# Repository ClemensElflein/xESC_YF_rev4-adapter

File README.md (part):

<!-- PROJECT SHIELDS -->
<!--
- Markdown "reference style" links for readability.
- Reference links are enclosed in brackets [ ] instead of parentheses ( ).
  (See the bottom of this document for the declaration of the reference variables)
-->
[![Contributors][contributors-shield]][contributors-url]
[![Forks][forks-shield]][forks-url]
[![Stargazers][stars-shield]][stars-url]
[![Issues][issues-shield]][issues-url]
[![MIT License][license-shield]][license-url]

<!-- PROJECT LOGO -->
<br />
<div align="center">
<h3 align="center">xESC YardForce (Rev4) adapter for <a href="https://github.com/ClemensElflein/OpenMower">OpenMower</a></h3>

  <p align="center">
    Simple xESC adapter for stock Rev4 (built 2017) blade-motor<br>
    (the one with an internal motor controller under its cap)
    <br />
  </p>

  |             v1.x Hardware              |             v2.x Hardware              |
  | :------------------------------------: | :------------------------------------: |
  |  |  |

</div>

<!-- ABOUT THE PROJECT -->
## About The Project

Those who want to use <a href="https://github.com/ClemensElflein/OpenMower">OpenMower</a> with an older YardForce "Rev. 4" (built 2017) model, fail with the stock Blade-Motor as it has an embedded motor-controller under its cap.

It's not very difficult to use this motor:
- Remove stock driver controller
- Wire the coil cables directly
- Add a 5 pin cable to the motor hall sensors
- Connect them to OM's mow-motor-hall-input plug
and use OM's xESC.

But it's somehow "crafted" and you need to be capable to do these things.

As an alternative, this "Adapter" is thought to replace OM's default Mow- xESC.<br>
In addition to this adapter, it's nevertheless **required to exchange two cables of the mow motor cabling**. But this should be also possible for the untalented (see [Requirements](#requirements)).

<p align="right">(<a href="#readme-top">back to top</a>)</p>

## Requirements

**It's mandatory to cross the green and black mow-motor-cables!**

> [!WARNING]  
> **Never** plug or un-plug the mow-motor while the adapter is powered!

> [!WARNING]  
> Do **not** simply trust the cable colors!<br>
> Check the image and validate if your
> cables do have the same colors! If not adapt accordingly

Either exchange the pins within the plug, or do it the lazy way like me, with a screw terminal block.
The latter has the advantage that you immediately see that you already crossed green/black.

## Prerequisites

* The compiled firmware from the [Releases](https://github.com/ClemensElflein/xESC_YF_rev4-adapter/releases) section. Use the `latest` pre-release for the newest development build, or a tagged release (e.g. `v0.4.0`) for a released version. Download and unzip `firmware_xesc-yf-rev4*.zip`; it contains the firmware for both hardware versions:
  * `firmware_xesc_yf_rev4_v1.bin` - hardware v1.x
  * `firmware_xesc_yf_rev4_v2.bin` - hardware v2.x
* As of writing, your openmower image has to be on edge version >= commit [0bfd489](https://github.com/ClemensElflein/open_mower_ros/commit/0bfd489401b3e659d183e6c1f9b557cb0d59d3c1) which happened on 2024-07-04

## Firmware Installation

### Requirements

* You need an ST-Link debugger/programmer, like one of the cheap "ST-Link V2" probes from one of the big online retailer.
* [STLINK Tools](https://github.com/stlink-org/stlink) >= v1.8.0 (earlier versions do **not** support the used STM32C0x MCU)

### Hardware Version Branding

Starting with hardware version 2.0, the adapter's MCU needs to be branded by writing a hardware version record into the OTP area.

#### Branding Process:

1. **Generate** Hardware Version Binaries

   ```bash
   cd firmware/host-hw-config
   lbuild build
   scons
   ```

   This creates i.e.:
   - `hw_config_v1.0.bin` - Hardware v1.0 version record
   - `hw_config_v2.0.bin` - Hardware v2.0 version record
   - `hw_config_v2.1.bin` - Hardware v2.1 version record
  
1. **Connect your ST-Link** to the adapter PCB. Do **not** connect the 3.3V pin if your adapter is already assembled to the OpenMower Mainboard and gets powered by it!

1. **Write** Hardware Version Record

   ```bash
   # Write/brand v2.0 version record with ST-Link/V2
   STM32_Programmer_CLI -c port=SWD -d hw_config_v2.0.bin 0x1FFF7000

   # Write/brand v2.1 version record with ST-Link/V2 (R17 must be 510 Ω)
   STM32_Programmer_CLI -c port=SWD -d hw_config_v2.1.bin 0x1FFF7000
   ```

The branding process writes a small hardware version record to the first two OTP double words (64 bit each). **Take attention** that OTP can be written only once!

> [!WARNING]
> **Hardware v2.1.0** requires reworking the current-sense resistor **R17 = 510 Ω** (1 %, 0603).
> The firmware selects its analog profile from the OTP hardware version:
> v2.1 → 510 Ω / 2.0 A, everything else → 1 kΩ / 1.25 A.
> A v2.1 board **must** be branded with `hw_config_v2.1.bin` and needs firmware >= 0.4.0.

**Important Notes:**
- Branding only needs as well as "can" be done only **once per device**
- The branding **truly survives firmware updates** (because OTP can be written only once)
- Hardware Version 1.x boards don't need branding. Non-branded devices are assumed to be v1.0 hardware **by the v1 firmware**. A v2 binary treats a missing/invalid OTP record as wrong hardware (red LED on, motor disabled).
<br>
<br>

### Firmware Installation Variants

We have two options to install the firmware:<br>

<details>
<summary><b>ST-Link debugger/programmer</b> (OpenMower V1 and V2 hardware), for which you need to have access to the adapter PCB's SWDIO pins</summary>

### Firmware Installation via ST-Link debugger/programmer

#### Flash

1. Connect your ST-Link probe to the adapter PCB. Do **not** connect the 3.3V pin if your adapter is already assembled to the OpenMower Mainboard and gets powered by it!

2. Flash the adapter (use `firmware_xesc_yf_rev4_v1.bin` for HW v1.x):
   ```sh
   st-flash --reset write firmware_xesc_yf_rev4_v2.bin 0x08000000
   ```
   When done, st-flash should report 'Flash written and verified! jolly good!' (or similar) and immediately reboot.<br>

   **Only relevant for v1.x hardware:**

   > [!WARNING]  
   > Do not unplug now!
   
   On absolutely first firmware boot, it needs to flash some settings to the MCU. You'll see some blink codes.<br>
   Do NOT unplug till you see:
   - 3 simultaneous blinks of the green+red LED (=success), following of a
   - quick blink of the red LED (=no motor connected) as well as a
   - normal green blink (=ROS not connected).
   
   The whole procedure will only take about 10 seconds. Once the procedure got processed it won't get triggered again for this MCU on future firmware flashes.

   If the board doesn't come up with blink signs, unplug and replug it. But once you see blink signs, do **not** unplug it before getting the described LED codes of the previous paragraph.   

</details>

<details>
<summary><b>Serial UART connection</b> (OpenMower V1 hardware only) via STM32 internal bootloader</summary>

### Firmware Installation via serial connection (UART)

Firmware flashing via UART is currently only possible with OpenMower V1 based hardware; on V2 carrier boards use the ST-Link/SWD path (Variant A).

#### Requirements

* [STM32CubeProgrammer](https://www.st.com/en/development-tools/stm32cubeprog.html) is the tool we need to flash via UART. But because we like to use it with our OpenMower's Raspberry-Pi, we need it in `aarch64` architecture. Unfortunately (as well as unbelievable) ST's programmer tool for ARM CPU's isn't available *for* ARM CPU's/architectures!!<br>
So we need to trick a little bit, and for this you need a non-arm Linux machine (x86_64).<br>
  1. Download [STM32CubePrg-Lin](https://www.st.com/en/development-tools/stm32cubeprog.html) package with (or to) a x86_64 Linux machine
  2. Unpack and install it on the x86_64 Linux machine
  3. Pack (zip, tar, ...) the installed binaries from where you just installed them
  4. Copy that package to your Raspberry-Pi and unpack it to somewhere. I placed mine to /opt/STM32CubeProgrammer
* [box64](https://github.com/ptitSeb/box64) to be able to run the STM32CubeProgrammer's x86_64 binary with our aarch64 architecture.<br>
Luckily they do have pre-build [Debian packages](https://github.com/ptitSeb/box64/blob/main/docs/COMPILE.md#debian-based-linux). Please follow their instruction.

Once *box64* got installed, you should be able to start the STM32Programmer CLI i.e. via: `/opt/STM32CubeProgrammer/bin/STM32_Programmer_CLI`

#### Flash

1. Login to your OpenMower Raspberry-Pi and stop openmower:<br>
   `sudo systemctl stop openmower`
   
2. Configure Raspberry-PI's serial device where the adapter is connected to, which is normally */dev/ttyAMA3*:<br>
   `stty -F /dev/ttyAMA3 115200 raw`
   
3. Now trigger the current running adapter firmware to do a reboot into the bootloader via:<br>
    `echo -e "\x00Reboot into Bootloader" > /dev/ttyAMA3`

4. Check if STM32 MCU is now in bootloader mode (Step 3. was successful):<br>
   `/opt/STM32CubeProgrammer/bin/STM32_Programmer_CLI -c port=/dev/ttyAMA3`<br>
   Should output something like:<br>

   ```
      -------------------------------------------------------------------
                        STM32CubeProgrammer v2.16.0                  
      -------------------------------------------------------------------

   Serial Port /dev/ttyAMA3 is successfully opened.
   Port configuration: parity = even, baudrate = 115200, data-bit = 8,
                       stop-bit = 1.0, flow-control = off
   Activating device: OK
   Board       : --
   Chip ID: 0x443 
   BootLoader protocol version: 3.1
   Device name : STM32C01x
   Flash size  : 32 KBytes (default)
   Device type : MCU
   Revision ID : --  
   Device CPU  : Cortex-M0+
   ```

5. Flash:<br>
   `/opt/STM32CubeProgrammer/bin/STM32_Programmer_CLI -c port=/dev/ttyAMA3 -w firmware_xesc_yf_rev4_v2.bin 0x08000000`

6. Reset the device (start our newly flashed program):<br>
   `/opt/STM32CubeProgrammer/bin/STM32_Programmer_CLI -c port=/dev/ttyAMA3 --go 0x08000000`

   **Only relevant for v1.x hardware:**

   > [!WARNING]  
   > Do not power-off now!
   
   On absolutely first firmware boot, it needs to flash some settings to the MCU. You'll see some blink codes.<br>
   Do NOT unplug till you see:
   - 3 simultaneous blinks of the green+red LED (=success), following of a
   - quick blink of the red LED (=no motor connected) as well as a
   - normal green blink (=ROS not connected).
   
   The whole procedure will only take about 10 seconds. Once the procedure got processed it won't get triggered again for this MCU on future firmware flashes.

7. Finally start openmower again:<br>
   `sudo systemctl start openmower`

#### Alternative: native `stm32loader` (no box64)

[`stm32loader`](https://github.com/florisla/stm32loader) supports the STM32C0
bootloader and runs natively on the Raspberry Pi. Install `uv` once, then flash:

```bash
# one-time: install uv/uvx (official installer)
curl -LsSf https://astral.sh/uv/install.sh | sh

# flash (the three commands)
sudo systemctl stop openmower
stty -F /dev/ttyAMA3 115200 raw
echo -e "\x00Reboot into Bootloader" > /dev/ttyAMA3
uvx stm32loader -p /dev/ttyAMA3 -b 115200 -f C0 -e -w -v firmware_xesc_yf_rev4_v2.bin -g 0x08000000
sudo systemctl start openmower
```

Notes:
- Use `-e` (global mass erase), **not** `--auto-erase`; the C0 page size is not
  defined in `stm32loader`'s device table.
- The STM32CubeProgrammer method above is the tested fallback.
- The v1.x first-boot warning above applies to this method too.

</details>

<p align="right">(<a href="#readme-top">back to top</a>)</p>

## OpenMower Config

Choose the variant that matches your OpenMower mainboard:

<details>
<summary><b>OpenMower V1 based hardware</b> (mower_config)</summary>

### OpenMower V1 based Hardware (mower_config)

Lastly, you need to add the adapter to your mower_config. Here's the relevant section out of mower_config.sh.example:

```
# Select your ESC type
# Supported values as of today:
# xesc_mini: for the STM32 version (VESC)
# xesc_mini_w_r4ma: for the STM32 version (VESC), but with Rev4 (Mow) Motor Adapter (only available for YardForceSA650 mower type)
# xesc_2040: for the RP2040 version (very experimental!)
# xesc_2040_w_r4ma: for the RP2040 version (very experimental!), but with Rev4 (Mow) Motor Adapter (only available for YardForceSA650 mower type)
export OM_MOWER_ESC_TYPE="xesc_mini"
```

> [!IMPORTANT]
> For this adapter you have to use one of the `_w_r4ma` variants, i.e.
> `export OM_MOWER_ESC_TYPE="xesc_mini_w_r4ma"` (or `"xesc_2040_w_r4ma"` with an RP2040 based xESC)
> **and** `export OM_MOWER="YardForceSA650"`. Only that combination selects
> `comms_xesc_mini_w_r4ma_params.yaml`, which drives the mower ESC with the `xesc_yfr4` driver on `/dev/ttyAMA3`.
> The plain `xesc_mini` shown above is only the default of the example file.

Once adapted, restart openmower via: `sudo systemctl restart openmower`

</details>

<details>
<summary><b>OpenMower V2 based hardware</b> (xCore firmware)</summary>

### OpenMower V2 based Hardware (xCore Firmware)

Nothing to configure: as of OpenMower 1.6.x the matching firmware (`yardforce-v4`) is selected automatically.
Only for older versions, set it manually via `openmower configure env` → `FIRMWARE="yardforce-v4"`.

> [!NOTE]
> The adapter runs on OpenMower V2 hardware, but firmware updates via UART/bootloader are only available on V1. On V2 use ST-Link/SWD.

</details>

<p align="right">(<a href="#readme-top">back to top</a>)</p>

## LED codes

<table>
  <tr><th>White (Green)</th><th>Red</th><th>Description</th></tr>
  <tr><td colspan="2" align="center">3 * quick blink</td><td>'Power up' successful</td></tr>
  <tr><td>1Hz blink</td><td></td><td>Waiting for init by xesc_ros</td></tr>
  <tr><td>0.5Hz flash<br>(short flash every 2 seconds)</td><td></td><td>Shutdown (Sleep)</td></tr>
  <tr><td>on</td><td></td><td>All fine (initialized, xesc_ros connected and no error)</td></tr>  
  <tr><td></td><td>1Hz blink</td><td>Waiting for OpenMower (xesc_ros driver) connect</td></tr>
  <tr><td></td><td>flash</td><td>One single short flash for every host communication error, like packet or CRC error</td></tr>
  <tr><td></td><td>on</td><td><b>Wrong hardware version firmware flashed!</b><br>Motor disabled for safety. Flash correct firmware</td></tr>
  <tr><td></td><td>5 * blink</td><td>NRST Pin not yet disabled. <b>Keep board powered</b> and watch for further LED codes</td></tr>
  <tr><td>5 * blink</td><td></td><td>NRST successful flashed</td></tr>
  <tr><td></td><td>4Hz quick blink</td><td>Open VMC (no motor connected).<br> Keeps VMC off until a motor is connected, then clears by itself (~2 s).<br> <b>WARNING:</b> Do not connect the motor while the adapter is powered!</td></tr>
  <tr><td></td><td>2Hz fast blink</td><td>VMS temperature issue or over-current detected</td></tr>
</table>

<p align="right">(<a href="#readme-top">back to top</a>)</p>

## Self-Compile

This project is build with [modm](https://modm.io). You need to install the required toolchain as described in their [Installation](https://modm.io/guide/installation/) section, before going on. Note that modm's `repo.lb` additionally requires [GitPython](https://pypi.org/project/GitPython/): `pip3 install modm GitPython`.

Once done:

1. Clone this repository (inclusive submodules):<br>
  `git clone --recurse-submodules https://github.com/ClemensElflein/xESC_YF_rev4-adapter.git`
2. Change into the project source directory:<br>
  `cd xESC_YF_rev4-adapter/firmware/src`
3. Build the modm library files for a specific hardware version:<br>
   ```bash
   # This builds for HW v2.0 and v2.1 (same binary, profile selected via OTP)
   lbuild -c hw-v2.xml build
   ```
4. Compile the firmware:<br>
  `scons build profile=<release|debug>` builds the `.elf`, `scons build bin profile=<release|debug>` additionally creates the `.bin` (which is what `st-flash` needs, see above).
5. Flash firmware:<br>
  For STM32C0 support, [xPack OpenOCD](https://xpack-dev-tools.github.io/openocd-xpack/) **>= 0.12.0-3** is required. Either install your own one, or use the bundled one (linux-x64 only; on aarch64/Raspberry Pi use a native OpenOCD >= 0.12.0-3):<br>
  `export MODM_OPENOCD_BINARY=../packages/xpack-openocd-0.12.0-3-linux-x64/bin/openocd`<br>
  Afterwards flash the firmware via:<br>
  `scons program`<br>
  `scons program` runs `program ... verify` followed by `reset run`. With the ST-Link HLA driver, OpenOCD resets via SRST (NRST). If NRST is not connected (or disabled on v1.x), the MCU may not reset; connect NRST or power-cycle the board. `scons reset` uses the same SRST path.

<p align="right">(<a href="#readme-top">back to top</a>)</p>

## Roadmap

(Ordered by priority)

- [x] Design schematics and PCB 
- [x] Produce PCB
- [ ] Firmware 
    - [x] Generic VM control (on/off)
    - [x] Generic motor control (start, stop, break)
    - [x] Read SA, math RPM
    - [x] Open VMC (no motor connected) detection
    - [x] Disable NRST pin functionality
    - [x] Motor current consumption
    - [x] PCB temperature (junction temp of STM)
    - [x] Support shutdown signal
    - [ ] ~~Stock motor (wrong) cabling detection~~
    - [x] STM32 bootloader / flash via UART support (OpenMower V1 based mainboard)
    - [ ] UART flash support for OpenMower V2 based carrier-boards
- [x] ROS driver
    - [x] xesc_ros::xesc_yfr4
    - [x] Add RPM
- [x] OpenMower Hardware V2 firmware driver

See the [open issues](https://github.com/ClemensElflein/xESC_YF_rev4-adapter/issues) for a full list of proposed features (and known issues).

<p align="right">(<a href="#readme-top">back to top</a>)</p>

## History

### Firmware

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
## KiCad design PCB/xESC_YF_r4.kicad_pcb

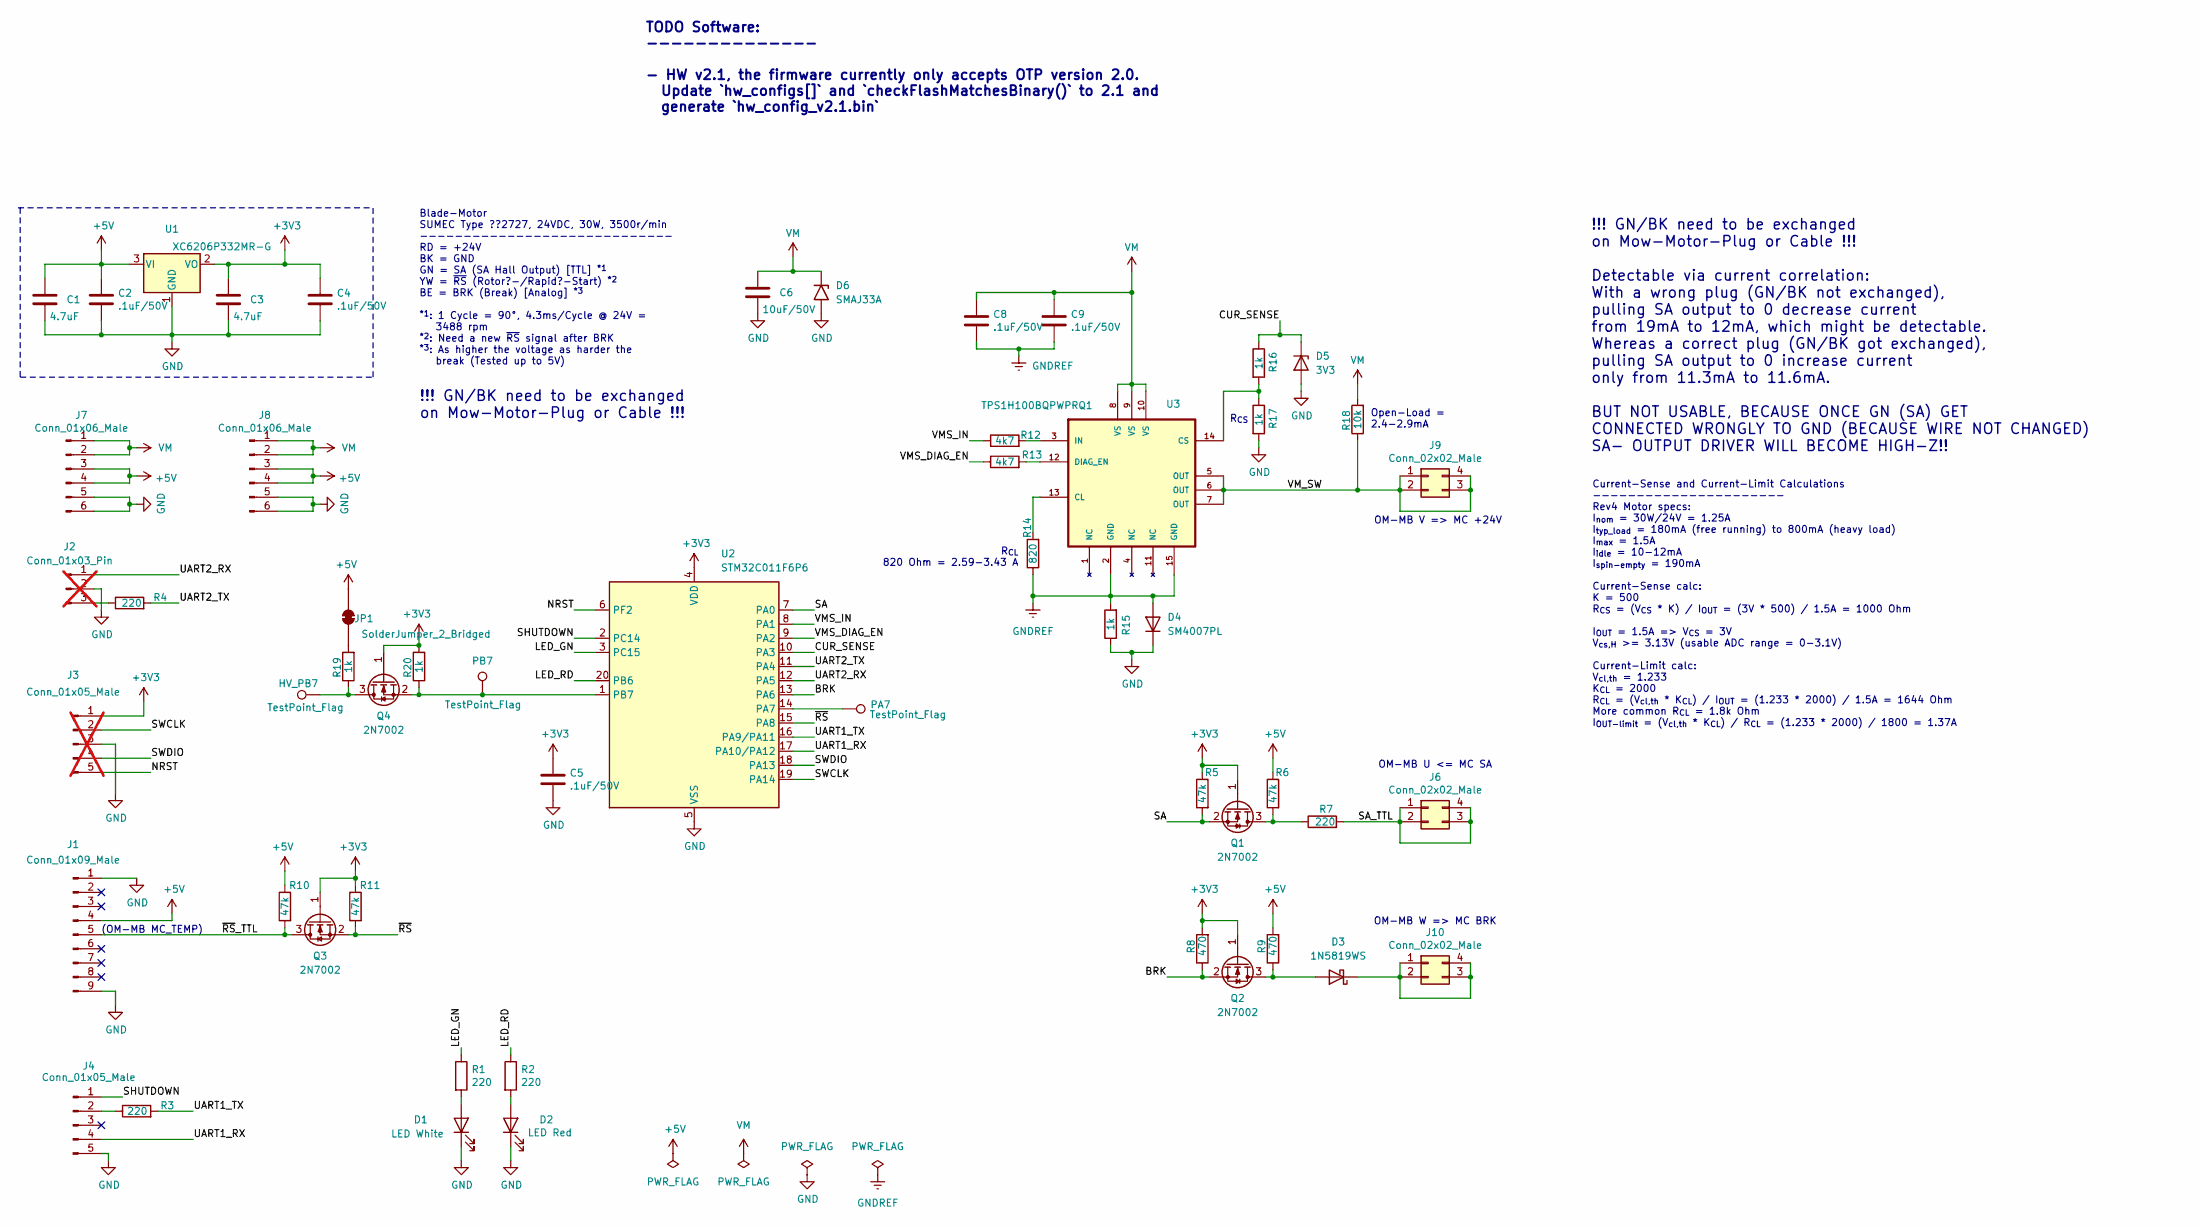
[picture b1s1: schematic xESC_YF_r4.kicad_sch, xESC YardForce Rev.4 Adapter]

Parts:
C1, C3: 4.7uF; C_0603_1608Metric; JLCPCB Part # C19666
C2, C4, C5, C8, C9: .1uF/50V; C_0402_1005Metric; MFR PART CL05B104KB54PNC; JLCPCB Part # C307331
C6: 10uF/50V; C_0805_2012Metric; JLCPCB Part # C440198
D1: LED White; LED_0603_1608Metric; MFR PART KT-0603W; JLCPCB Part # C2290
D2: LED Red; LED_0603_1608Metric; MFR PART KT-0603R; JLCPCB Part # C2286
D3: 1N5819WS; D_SOD-323; JLCPCB Part # C191023
D4: SM4007PL; D_SOD-123F; JLCPCB Part # C64898
D5: 3V3; D_SOD-123; MFR PART BZT52C3V3; JLCPCB Part # C19077396
D6: SMAJ33A; D_SMA; JLCPCB Part # C908777
HV_PB7: TestPoint_Flag; TestPoint_Pad_1.0x1.0mm
J1: Conn_01x09_Male; PinHeader_1x09_P2.54mm_Vertical; Part Number DZ254R-11-09-63; JLCPCB Part # C2935915
J2: Conn_01x03_Pin; PinHeader_1x03_P2.54mm_Vertical; not fitted
J3: Conn_01x05_Male; PinHeader_1x05_P2.54mm_Vertical; Part Number DZ254R-11-05-63; JLCPCB Part # C2935911; not fitted
J4: Conn_01x05_Male; PinHeader_1x05_P2.54mm_Vertical; Part Number DZ254R-11-05-63; JLCPCB Part # C2935911
J6, J9, J10: Conn_02x02_Male; PinHeader_2x02_P2.54mm_Vertical; Part Number B-2100S04P-B110; JLCPCB Part # C124362
J7, J8: Conn_01x06_Male; PinHeader_1x06_P2.54mm_Vertical; Part Number DZ254R-11-06-63; JLCPCB Part # C2935912
JP1: SolderJumper_2_Bridged; SolderJumper-2_P1.3mm_Bridged_RoundedPad1.0x1.5mm
PA7: TestPoint_Flag; TestPoint_Pad_1.0x1.0mm
PB7: TestPoint_Flag; TestPoint_Pad_1.0x1.0mm
Q1, Q2, Q3, Q4: 2N7002; SOT-23
R1, R2, R7: 220; R_0603_1608Metric; JLCPCB Part # C22962
R3, R4: 220; R_0603_1608Metric; Part Number 0603WAF2200T5E; JLCPCB Part # C22962
R5, R6, R10, R11: 47k; R_0603_1608Metric; Part Number 0603WAF4702T5E; JLCPCB Part # C25819
R8, R9: 470; R_0603_1608Metric; Part Number 0603WAF4700T5E; JLCPCB Part # C23179
R12, R13: 4k7; R_0603_1608Metric; Part Number 0603WAF4701T5E; JLCPCB Part # C23162
R14: 820; R_0603_1608Metric; Part Number 0603WAF8200T5E; JLCPCB Part # C23253
R15, R16, R17, R19, R20: 1k; R_0603_1608Metric; Part Number 0603WAF1001T5E; JLCPCB Part # C21190
R18: 10k; R_0805_2012Metric; Part Number 0805W8F1002T5E; JLCPCB Part # C17414
U1: XC6206P332MR-G; SOT-23-3; JLCPCB Part # C5446
U2: STM32C011F6P6; TSSOP-20_4.4x6.5mm_P0.65mm; JLCPCB Part # C5456198
U3: TPS1H100BQPWPRQ1; TPS1H100-Q1_ThermalVias; JLCPCB Part # C475505

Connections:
+3V3: C3.1, C4.1, C5.1, J3.1, Q1.1 (G), Q2.1 (G), Q3.1 (G), Q4.1 (G), R5.1, R8.2, R11.1, R20.2, U1.2 (VO), U2.4 (VDD)
+5V: C1.1, C2.1, J1.4, J7.3, J7.4, J8.3, J8.4, JP1.2 (B), R6.1, R9.2, R10.1, U1.3 (VI)
/BRK: Q2.2 (S), R8.1, U2.13 (PA6)
/CUR_SENSE: D5.1 (K), R16.1, U2.10 (PA3)
/LED_GN: R1.1, U2.3 (PC15)
/LED_RD: R2.1, U2.20 (PB6)
/NRST: J3.5, U2.6 (PF2)
/SA: Q1.2 (S), R5.2, U2.7 (PA0)
/SA_TTL: J6.1, J6.2, J6.3, J6.4, R7.2
/SHUTDOWN: J4.1, U2.2 (PC14)
/SWCLK: J3.2, U2.19 (PA14)
/SWDIO: J3.4, U2.18 (PA13)
/UART1_RX: J4.4, U2.17 (PA10/PA12)
/UART1_TX: R3.2, U2.16 (PA9/PA11)
/UART2_RX: J2.1, U2.12 (PA5)
/UART2_TX: R4.2, U2.11 (PA4)
/VMS_DIAG_EN: R13.1, U2.9 (PA2)
/VMS_IN: R12.1, U2.8 (PA1)
/VM_SW: J9.1, J9.2, J9.3, J9.4, R18.1, U3.5 (OUT), U3.6 (OUT), U3.7 (OUT)
/~RS: Q3.2 (S), R11.2, U2.15 (PA8)
/~RS_TTL: J1.5, Q3.3 (D), R10.2
GND: C1.2, C2.2, C3.2, C4.2, C5.2, C6.2, D1.1 (K), D2.1 (K), D4.1 (K), D5.2 (A), D6.2 (A2), J1.1, J1.9, J2.2, J3.3, J4.5, J7.5, J7.6, J8.5, J8.6, R15.1, R17.2, U1.1 (GND), U2.5 (VSS)
GNDREF: C8.2, C9.2, D4.2 (A), R14.1, R15.2, U3.2 (GND), U3.15 (GND)
unnamed: D1.2 (A), R1.2
unnamed: D2.2 (A), R2.2
unnamed: D3.2 (A), Q2.3 (D), R9.1
unnamed: D3.1 (K), J10.1, J10.2, J10.3, J10.4
unnamed: J2.3, R4.1
unnamed: J4.2, R3.1
unnamed: JP1.1 (A), R19.2
unnamed: Q1.3 (D), R6.2, R7.1
unnamed: HV_PB7.1 (1_1), Q4.3 (D), R19.1
unnamed: PB7.1 (1_1), Q4.2 (S), R20.1, U2.1 (PB7)
unnamed: PA7.1 (1_1), U2.14 (PA7)
unnamed: R14.2, U3.13 (CL)
unnamed: R16.2, R17.1, U3.14 (CS)
unnamed: R13.2, U3.12 (DIAG_EN)
unnamed: R12.2, U3.3 (IN)
VM: C6.1, C8.1, C9.1, D6.1 (A1), J7.1, J7.2, J8.1, J8.2, R18.2, U3.8 (VS), U3.9 (VS), U3.10 (VS)

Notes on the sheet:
(OM-MB MC_TEMP)
OM-MB V => MC +24V
Current-Sense and Current-Limit Calculations ---------------------- Rev4 Motor specs: I_{nom} = 30W/24V = 1.25A I_{typ_load} = 180mA (free running) to 800mA (heavy load) I_{max} = 1.5A I_{idle} = 10-12mA I_{spin-empty} = 190mA Current-Sense calc: K = 500 R_{CS} = (V_{CS} * K) / I_{OUT} = (3V * 500)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
OM-MB W => MC BRK
!!! GN/BK need to be exchanged on Mow-Motor-Plug or Cable !!! Detectable via current correlation: With a wrong plug (GN/BK not exchanged), pulling SA output to 0 decrease current from 19mA to 12mA, which might be detectable. Whereas a correct plug (GN/BK got exchanged), pulling SA output to 0 incre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
OM-MB U <= MC SA
Open-Load = 2.4-2.9mA
Blade-Motor SUMEC Type ??2727, 24VDC, 30W, 3500r/min ----------------------------- RD = +24V BK = GND GN = SA (SA Hall Output) [TTL] ^{*1} YW = ~{RS} (Rotor?-/Rapid?-Start) ^{*2} BE = BRK (Break) [Analog] ^{*3} ^{*1}: 1 Cycle = 90°, 4.3ms/Cycle @ 24V = 3488 rpm ^{*2}: Need a new ~{RS} signal after 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
!!! GN/BK need to be exchanged on Mow-Motor-Plug or Cable !!!
R_{CL} 820 Ohm = 2.59-3.43 A
TODO Software: -------------- - HW v2.1, the firmware currently only accepts OTP version 2.0. Update `hw_configs[]` and `checkFlashMatchesBinary()` to 2.1 and generate `hw_config_v2.1.bin`
R_{CS}

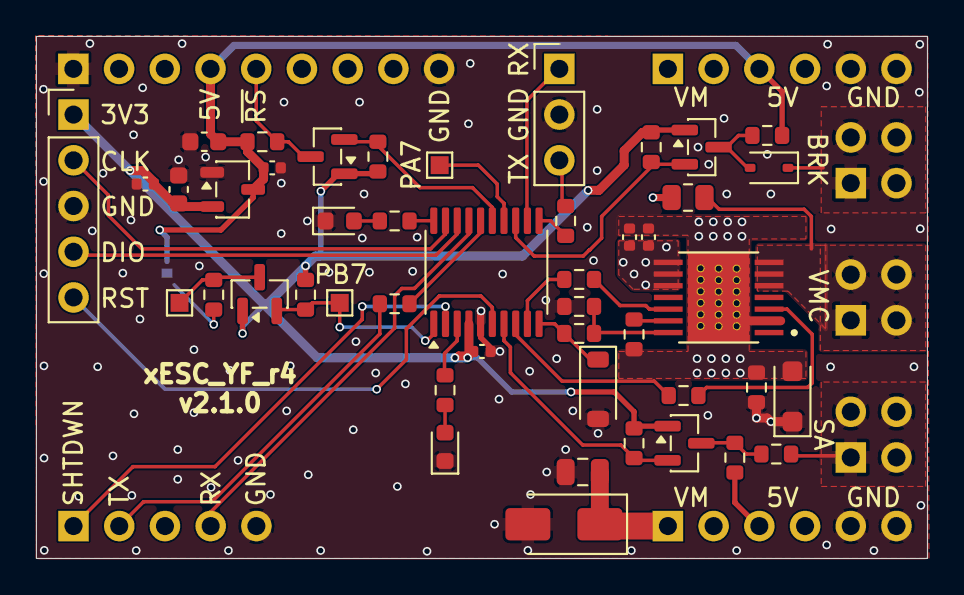
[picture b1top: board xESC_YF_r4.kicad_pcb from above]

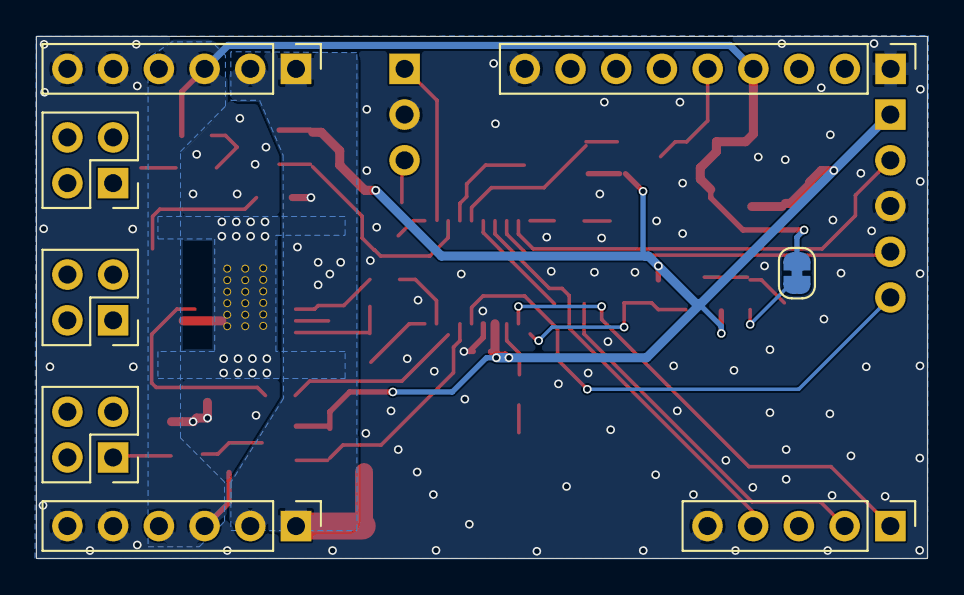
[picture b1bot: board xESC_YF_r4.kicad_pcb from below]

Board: 2 copper layers, 49.5 x 29.0 mm, 54 parts (8 on the bottom side), 39 nets.

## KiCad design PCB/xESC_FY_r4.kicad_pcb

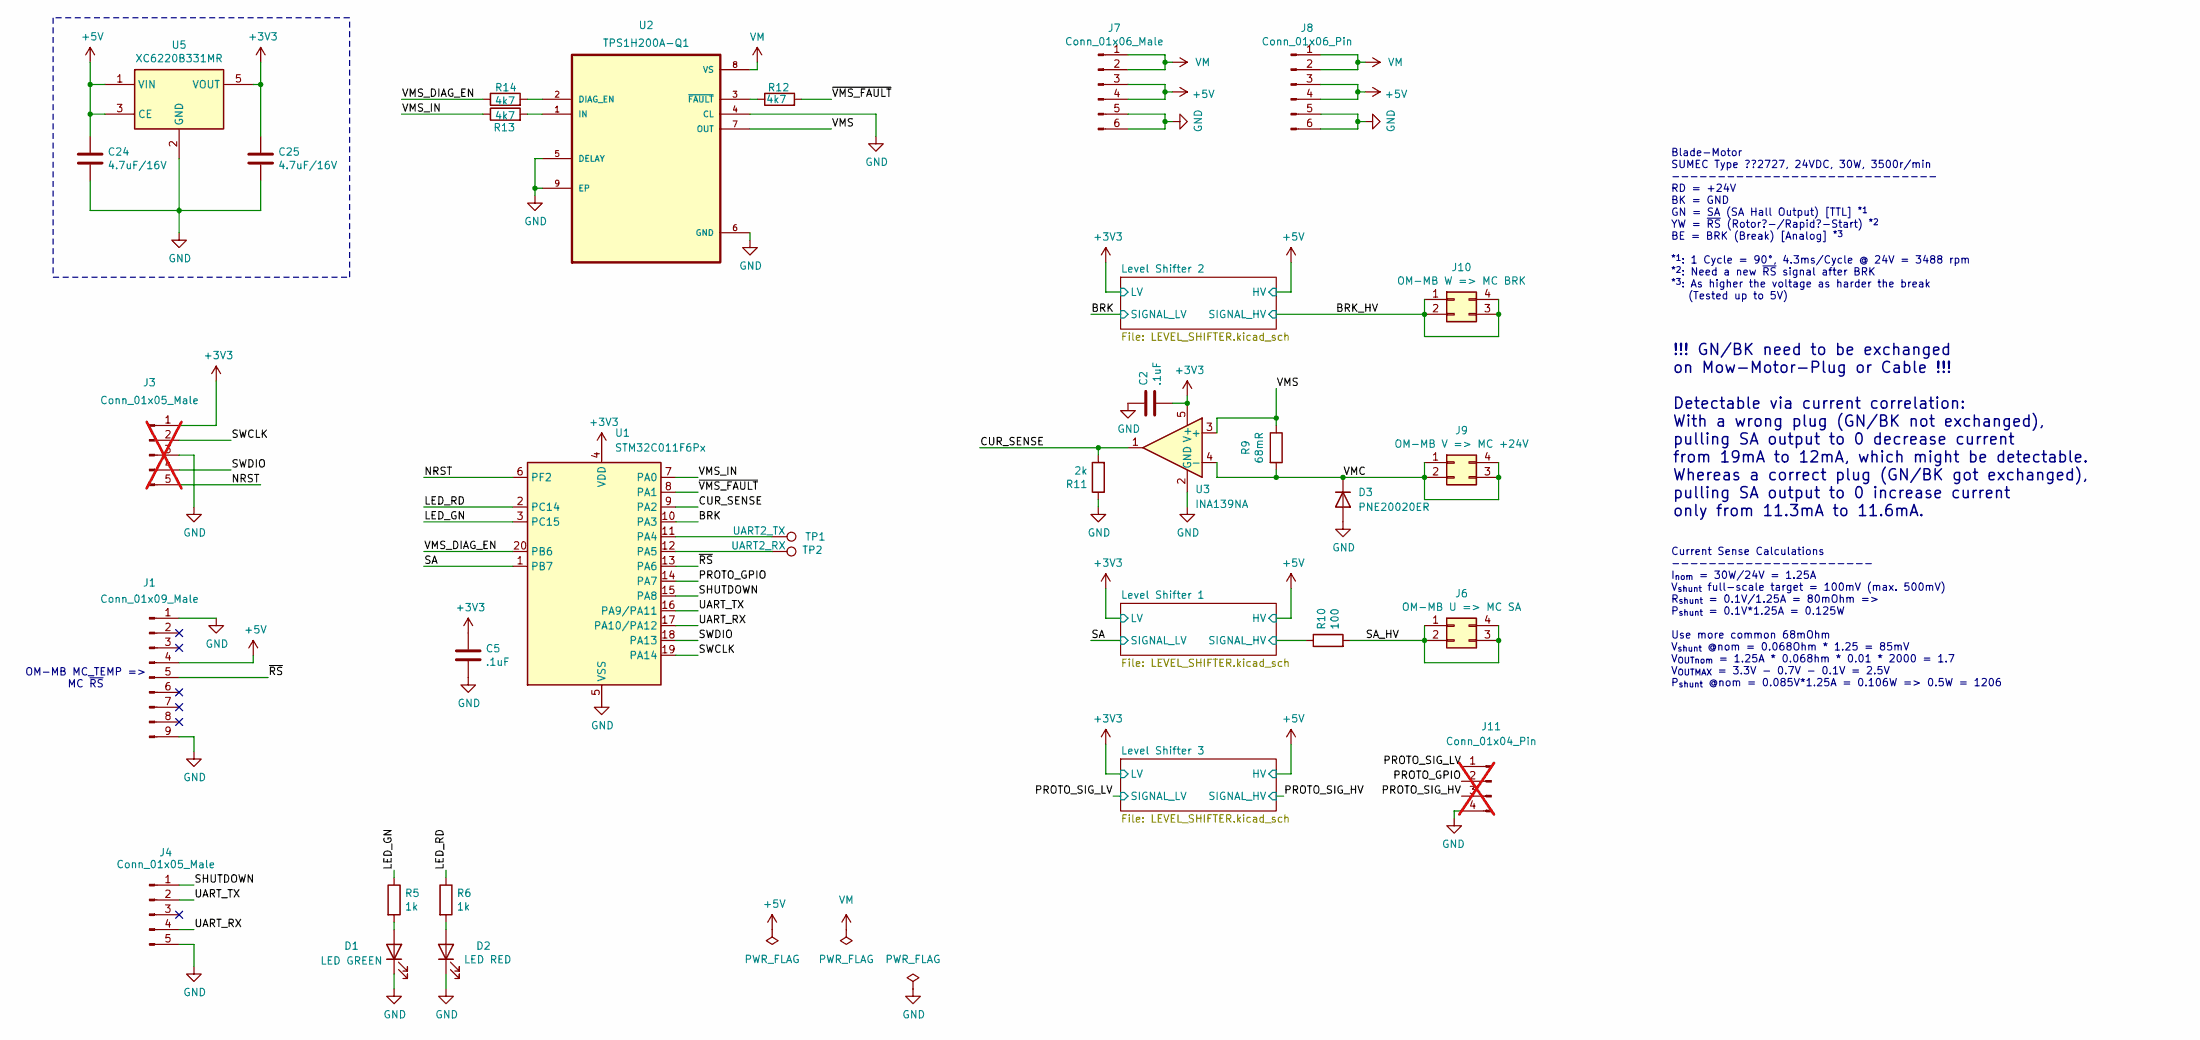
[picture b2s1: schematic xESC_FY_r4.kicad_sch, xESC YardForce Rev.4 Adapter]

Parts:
C2, C5: .1uF; C_0603_1608Metric; Part Number CL10B104KC8NNNC; Digikey 1276-1935-1-ND
C24, C25: 4.7uF/16V; C_0603_1608Metric; Part Number CL21A106KOQNNNE; Digikey 1276-1096-2-ND
D1: LED GREEN; LED_0603_1608Metric; Part Number LTST-C191KGKT; Digikey 160-1446-1-ND
D2: LED RED; LED_0603_1608Metric; Part Number LTST-C191KRKT; Digikey 160-1447-1-ND
D3: PNE20020ER; Nexperia_CFP3_SOD-123W
J1: Conn_01x09_Male; PinHeader_1x09_P2.54mm_Vertical; Part Number DZ254R-11-09-63; LCSC C2935915
J3: Conn_01x05_Male; PinHeader_1x05_P2.54mm_Vertical; Part Number DZ254R-11-05-63; LCSC C2935911; not fitted
J4: Conn_01x05_Male; PinHeader_1x05_P2.54mm_Vertical; Part Number DZ254R-11-05-63; LCSC C2935911
J6: OM-MB U => MC SA; PinHeader_2x02_P2.54mm_Vertical; Part Number B-2100S04P-B110; LCSC C124362
J7: Conn_01x06_Male; PinHeader_1x06_P2.54mm_Vertical; Part Number DZ254R-11-06-63; LCSC C2935912
J8: Conn_01x06_Pin; PinHeader_1x06_P2.54mm_Vertical; Part Number DZ254R-11-06-63; LCSC C2935912
J9: OM-MB V => MC +24V; PinHeader_2x02_P2.54mm_Vertical; Part Number B-2100S04P-B110; LCSC C124362
J10: OM-MB W => MC BRK; PinHeader_2x02_P2.54mm_Vertical; Part Number B-2100S04P-B110; LCSC C124362
J11: Conn_01x04_Pin; PinHeader_1x04_P2.54mm_Vertical; not fitted
R5, R6: 1k; R_0603_1608Metric; Part Number RC0603FR-07150RL; Digikey 311-150HRCT-ND
R9: 68mR; R_1206_3216Metric_Pad1.30x1.75mm_HandSolder; Part Number KDV12FR068ET; JLCPCB C2442650
R10: 100; R_0603_1608Metric
R11: 2k; R_0603_1608Metric
R12, R13, R14: 4k7; R_0603_1608Metric; Part Number RC0603FR-07150RL; Digikey 311-150HRCT-ND
TP1: UART2_TX; TestPoint_Pad_1.5x1.5mm
TP2: UART2_RX; TestPoint_Pad_1.5x1.5mm
U1: STM32C011F6Px; TSSOP-20_4.4x6.5mm_P0.65mm
U2: TPS1H200A-Q1; SOP65P490X110-9N-AHMOD
U3: INA139NA; SOT-23-5
U5: XC6220B331MR; SOT-23-5; Part Number XC6220B331MR; Digikey 893-1133-1-ND

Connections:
+3V3: C2.2, C5.1, C25.1, J3.1, U1.4 (VDD), U3.5 (V+), U5.5 (VOUT); also elsewhere on the board
+5V: C24.1, J1.4, J7.3, J7.4, J8.3, J8.4, U5.1 (VIN), U5.3 (CE); also elsewhere on the board
/BRK: U1.10 (PA3); also elsewhere on the board
/BRK_HV: J10.1, J10.2, J10.3, J10.4; also elsewhere on the board
/CUR_SENSE: R11.2, U1.9 (PA2), U3.1
/LED_GN: R5.1, U1.3 (PC15)
/LED_RD: R6.1, U1.2 (PC14)
/Level Shifter 1/SIGNAL_HV: R10.1; also elsewhere on the board
/NRST: J3.5, U1.6 (PF2)
/PROTO_GPIO: J11.2, U1.14 (PA7)
/PROTO_SIG_HV: J11.3; also elsewhere on the board
/PROTO_SIG_LV: J11.1; also elsewhere on the board
/SA: U1.1 (PB7); also elsewhere on the board
/SA_HV: J6.1, J6.2, J6.3, J6.4, R10.2
/SHUTDOWN: J4.1, U1.15 (PA8)
/SWCLK: J3.2, U1.19 (PA14)
/SWDIO: J3.4, U1.18 (PA13)
/UART_RX: J4.4, U1.17 (PA10/PA12)
/UART_TX: J4.2, U1.16 (PA9/PA11)
/VMC: D3.1 (K), J9.1, J9.2, J9.3, J9.4, R9.2, U3.4 (-)
/VMS: R9.1, U2.7 (OUT), U3.3 (+)
/VMS_DIAG_EN: R14.1, U1.20 (PB6)
/VMS_IN: R13.1, U1.7 (PA0)
/~RS: J1.5, U1.13 (PA6)
/~VMS_FAULT: R12.2, U1.8 (PA1)
GND: C2.1, C5.2, C24.2, C25.2, D1.1 (K), D2.1 (K), D3.2 (A), J1.1, J1.9, J3.3, J4.5, J7.5, J7.6, J8.5, J8.6, J11.4, R11.1, U1.5 (VSS), U2.4 (CL), U2.5 (DELAY), U2.6 (GND), U2.9 (EP), U3.2 (GND), U5.2 (GND)
unnamed: D1.2 (A), R5.2
unnamed: D2.2 (A), R6.2
unnamed: TP1.1, U1.11 (PA4)
unnamed: TP2.1, U1.12 (PA5)
unnamed: R14.2, U2.2 (DIAG_EN)
unnamed: R13.2, U2.1 (IN)
unnamed: R12.1, U2.3 (~FAULT)
VM: J7.1, J7.2, J8.1, J8.2, U2.8 (VS)

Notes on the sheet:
OM-MB MC_TEMP => MC ~{RS}
Blade-Motor SUMEC Type ??2727, 24VDC, 30W, 3500r/min ----------------------------- RD = +24V BK = GND GN = SA (SA Hall Output) [TTL] ^{*1} YW = ~{RS} (Rotor?-/Rapid?-Start) ^{*2} BE = BRK (Break) [Analog] ^{*3} ^{*1}: 1 Cycle = 90°, 4.3ms/Cycle @ 24V = 3488 rpm ^{*2}: Need a new ~{RS} signal after 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
!!! GN/BK need to be exchanged on Mow-Motor-Plug or Cable !!! Detectable via current correlation: With a wrong plug (GN/BK not exchanged), pulling SA output to 0 decrease current from 19mA to 12mA, which might be detectable. Whereas a correct plug (GN/BK got exchanged), pulling SA output to 0 incre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
Current Sense Calculations ---------------------- I_{nom} = 30W/24V = 1.25A V_{shunt} full-scale target = 100mV (max. 500mV) R_{shunt} = 0.1V/1.25A = 80mOhm => P_{shunt} = 0.1V*1.25A = 0.125W Use more common 68mOhm V_{shunt} @nom = 0.068Ohm * 1.25 = 85mV V_{OUTnom} = 1.25A * 0.068hm * 0.01 * 2000 =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

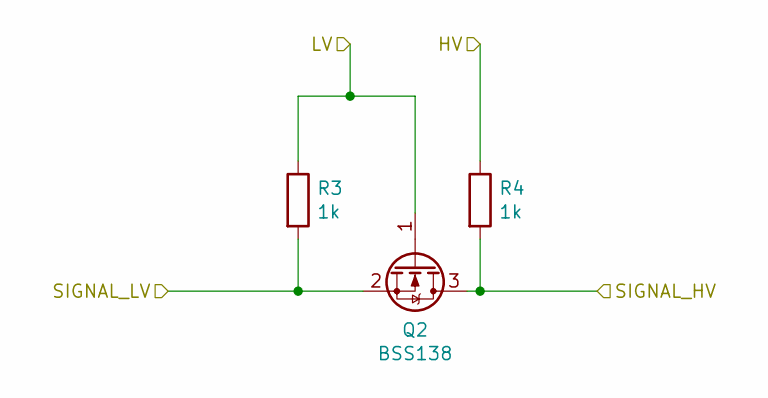
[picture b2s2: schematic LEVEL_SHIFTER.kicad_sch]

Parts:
Q2: BSS138; SOT-23; Part Number AP2300; LCSC C3040446
R3, R4: 1k; R_0805_2012Metric_Pad1.20x1.40mm_HandSolder; Part Number RC0805FR-071KL; Digikey 311-1.00KCRCT-ND

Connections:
+3V3: Q2.1 (G), R3.1; also elsewhere on the board
+5V: R4.1; also elsewhere on the board
/BRK: Q2.2 (S), R3.2; also elsewhere on the board
/BRK_HV: Q2.3 (D), R4.2; also elsewhere on the board

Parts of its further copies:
Q1, Q3: BSS138; SOT-23; Part Number AP2300; LCSC C3040446
R1, R2, R7, R8: 1k; R_0805_2012Metric_Pad1.20x1.40mm_HandSolder; Part Number RC0805FR-071KL; Digikey 311-1.00KCRCT-ND

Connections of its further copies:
+3V3: Q1.1 (G), Q3.1 (G), R1.1, R7.1; also elsewhere on the board
+5V: R2.1, R8.1; also elsewhere on the board
/Level Shifter 1/SIGNAL_HV: Q1.3 (D), R2.2; also elsewhere on the board
/PROTO_SIG_HV: Q3.3 (D), R8.2; also elsewhere on the board
/PROTO_SIG_LV: Q3.2 (S), R7.2; also elsewhere on the board
/SA: Q1.2 (S), R1.2; also elsewhere on the board

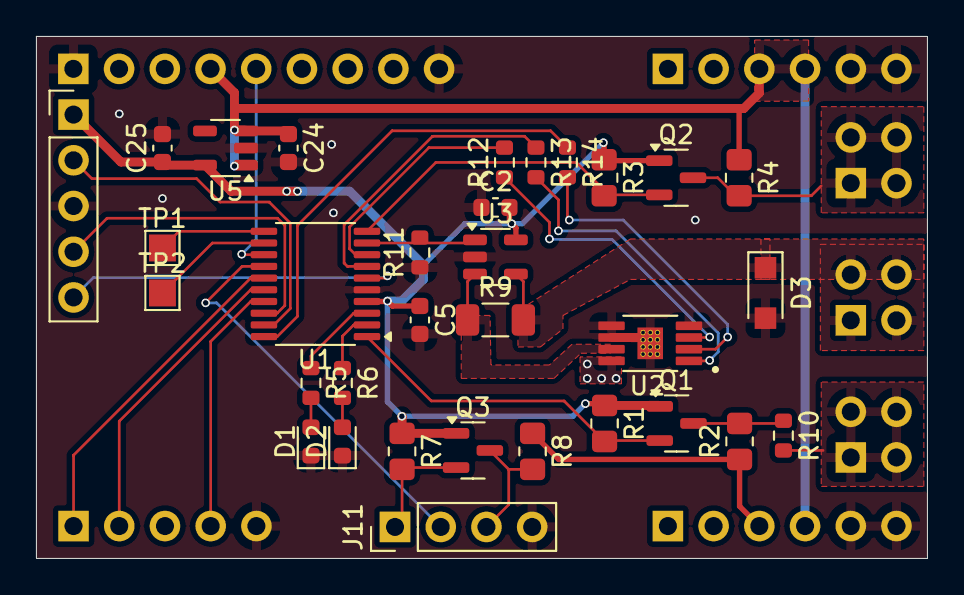
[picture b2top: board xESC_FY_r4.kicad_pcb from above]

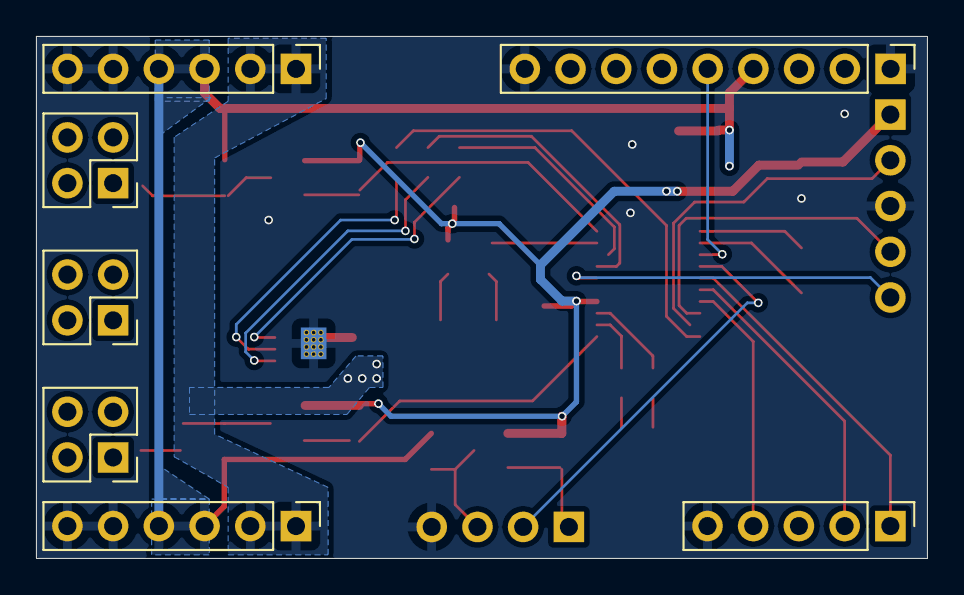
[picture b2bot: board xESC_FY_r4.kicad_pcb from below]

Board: 2 copper layers, 49.5 x 29.0 mm, 39 parts (7 on the bottom side), 34 nets.

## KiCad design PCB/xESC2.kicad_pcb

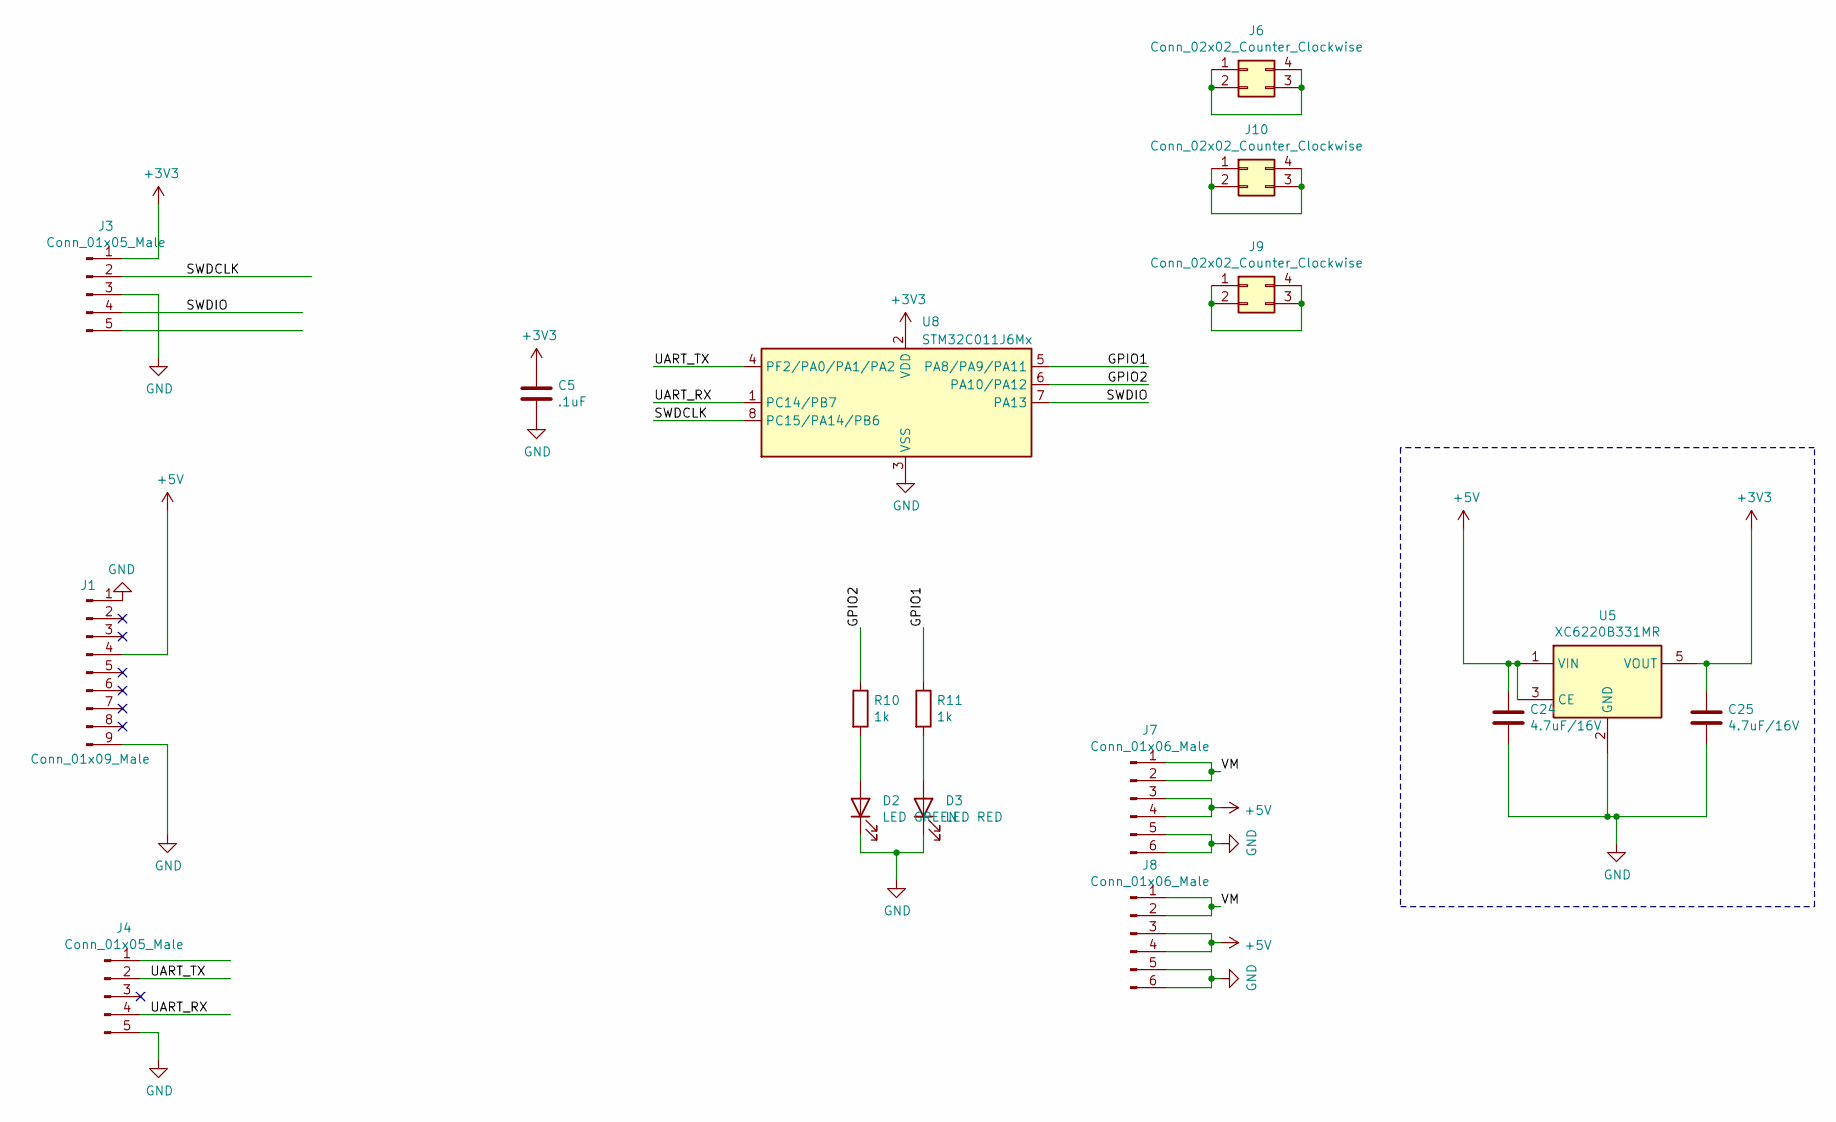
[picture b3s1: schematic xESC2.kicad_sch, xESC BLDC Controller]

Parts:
C5: .1uF; C_0603_1608Metric; Part Number CL10B104KC8NNNC; Digikey 1276-1935-1-ND
C24, C25: 4.7uF/16V; C_0603_1608Metric; Part Number CL21A106KOQNNNE; Digikey 1276-1096-2-ND
D2: LED GREEN; LED_0603_1608Metric; Part Number LTST-C191KGKT; Digikey 160-1446-1-ND
D3: LED RED; LED_0603_1608Metric; Part Number LTST-C191KRKT; Digikey 160-1447-1-ND
J1: Conn_01x09_Male; PinHeader_1x09_P2.54mm_Vertical; Part Number DZ254R-11-09-63; LCSC C2935915
J3, J4: Conn_01x05_Male; PinHeader_1x05_P2.54mm_Vertical; Part Number DZ254R-11-05-63; LCSC C2935911
J6, J9, J10: Conn_02x02_Counter_Clockwise; PinHeader_2x02_P2.54mm_Vertical; Part Number B-2100S04P-B110; LCSC C124362
J7, J8: Conn_01x06_Male; PinHeader_1x06_P2.54mm_Vertical; Part Number DZ254R-11-06-63; LCSC C2935912
R10, R11: 1k; R_0603_1608Metric; Part Number RC0603FR-07150RL; Digikey 311-150HRCT-ND
U5: XC6220B331MR; SOT-23-5; Part Number XC6220B331MR; Digikey 893-1133-1-ND
U8: STM32C011J6Mx; SOIC-8_3.9x4.9mm_P1.27mm

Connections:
+3V3: C5.1, C25.1, J3.1, U5.5 (VOUT), U8.2 (VDD)
+5V: C24.1, J1.4, J7.3, J7.4, J8.3, J8.4, U5.1 (VIN), U5.3 (CE)
/GPIO1: R11.1, U8.5 (PA8/PA9/PA11)
/GPIO2: R10.1, U8.6 (PA10/PA12)
/SWDCLK: J3.2, U8.8 (PC15/PA14/PB6)
/SWDIO: J3.4, U8.7 (PA13)
/UART_RX: J4.4, U8.1 (PC14/PB7)
/UART_TX: J4.2, U8.4 (PF2/PA0/PA1/PA2)
/VM: J7.1, J7.2, J8.1, J8.2
GND: C5.2, C24.2, C25.2, D2.1 (K), D3.1 (K), J1.1, J1.9, J3.3, J4.5, J7.5, J7.6, J8.5, J8.6, U5.2 (GND), U8.3 (VSS)
unnamed: D2.2 (A), R10.2
unnamed: D3.2 (A), R11.2
unnamed: J6.1, J6.2, J6.3, J6.4
unnamed: J9.1, J9.2, J9.3, J9.4
unnamed: J10.1, J10.2, J10.3, J10.4

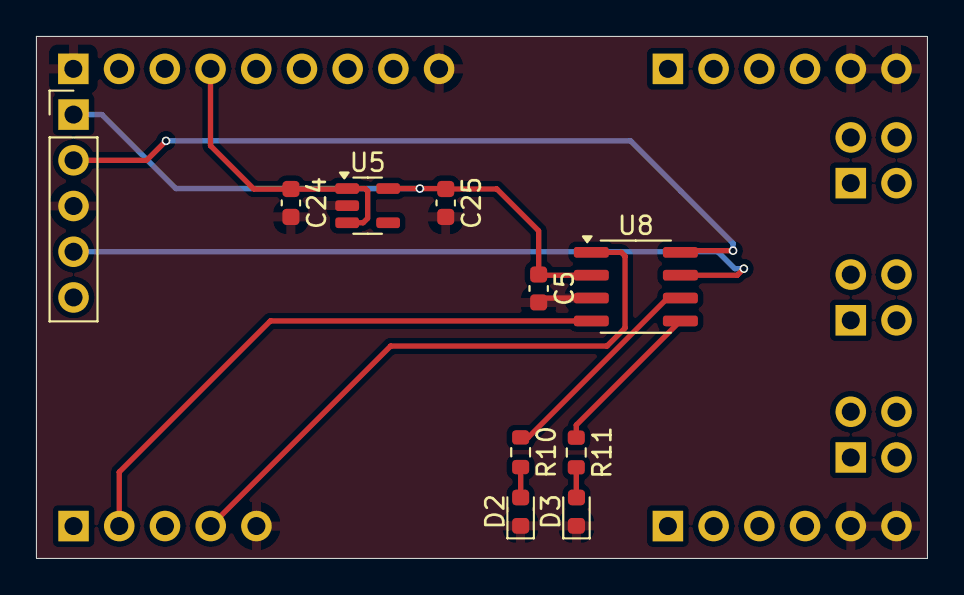
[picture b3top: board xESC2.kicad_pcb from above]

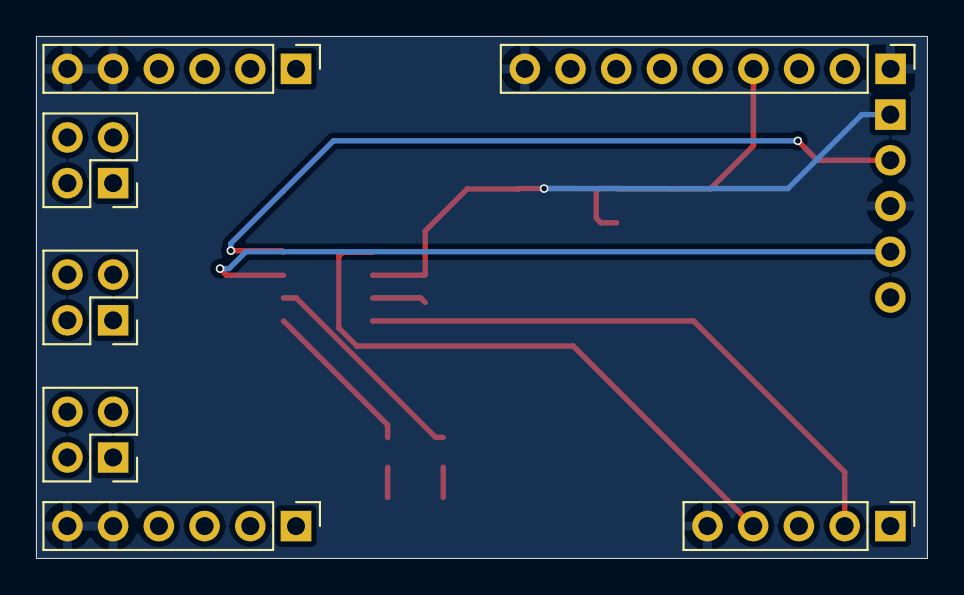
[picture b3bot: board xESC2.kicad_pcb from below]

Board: 4 copper layers, 49.5 x 29.0 mm, 17 parts (7 on the bottom side), 15 nets.

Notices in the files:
README.md:
License:
Distributed under the MIT License. See [LICENSE](LICENSE) for more information.
PCB/v1.0/xESC_YF_r4.kicad_sch:
Creative Commons Attribution-NonCommercial-ShareAlike 4.0 International License.
Licensed under
